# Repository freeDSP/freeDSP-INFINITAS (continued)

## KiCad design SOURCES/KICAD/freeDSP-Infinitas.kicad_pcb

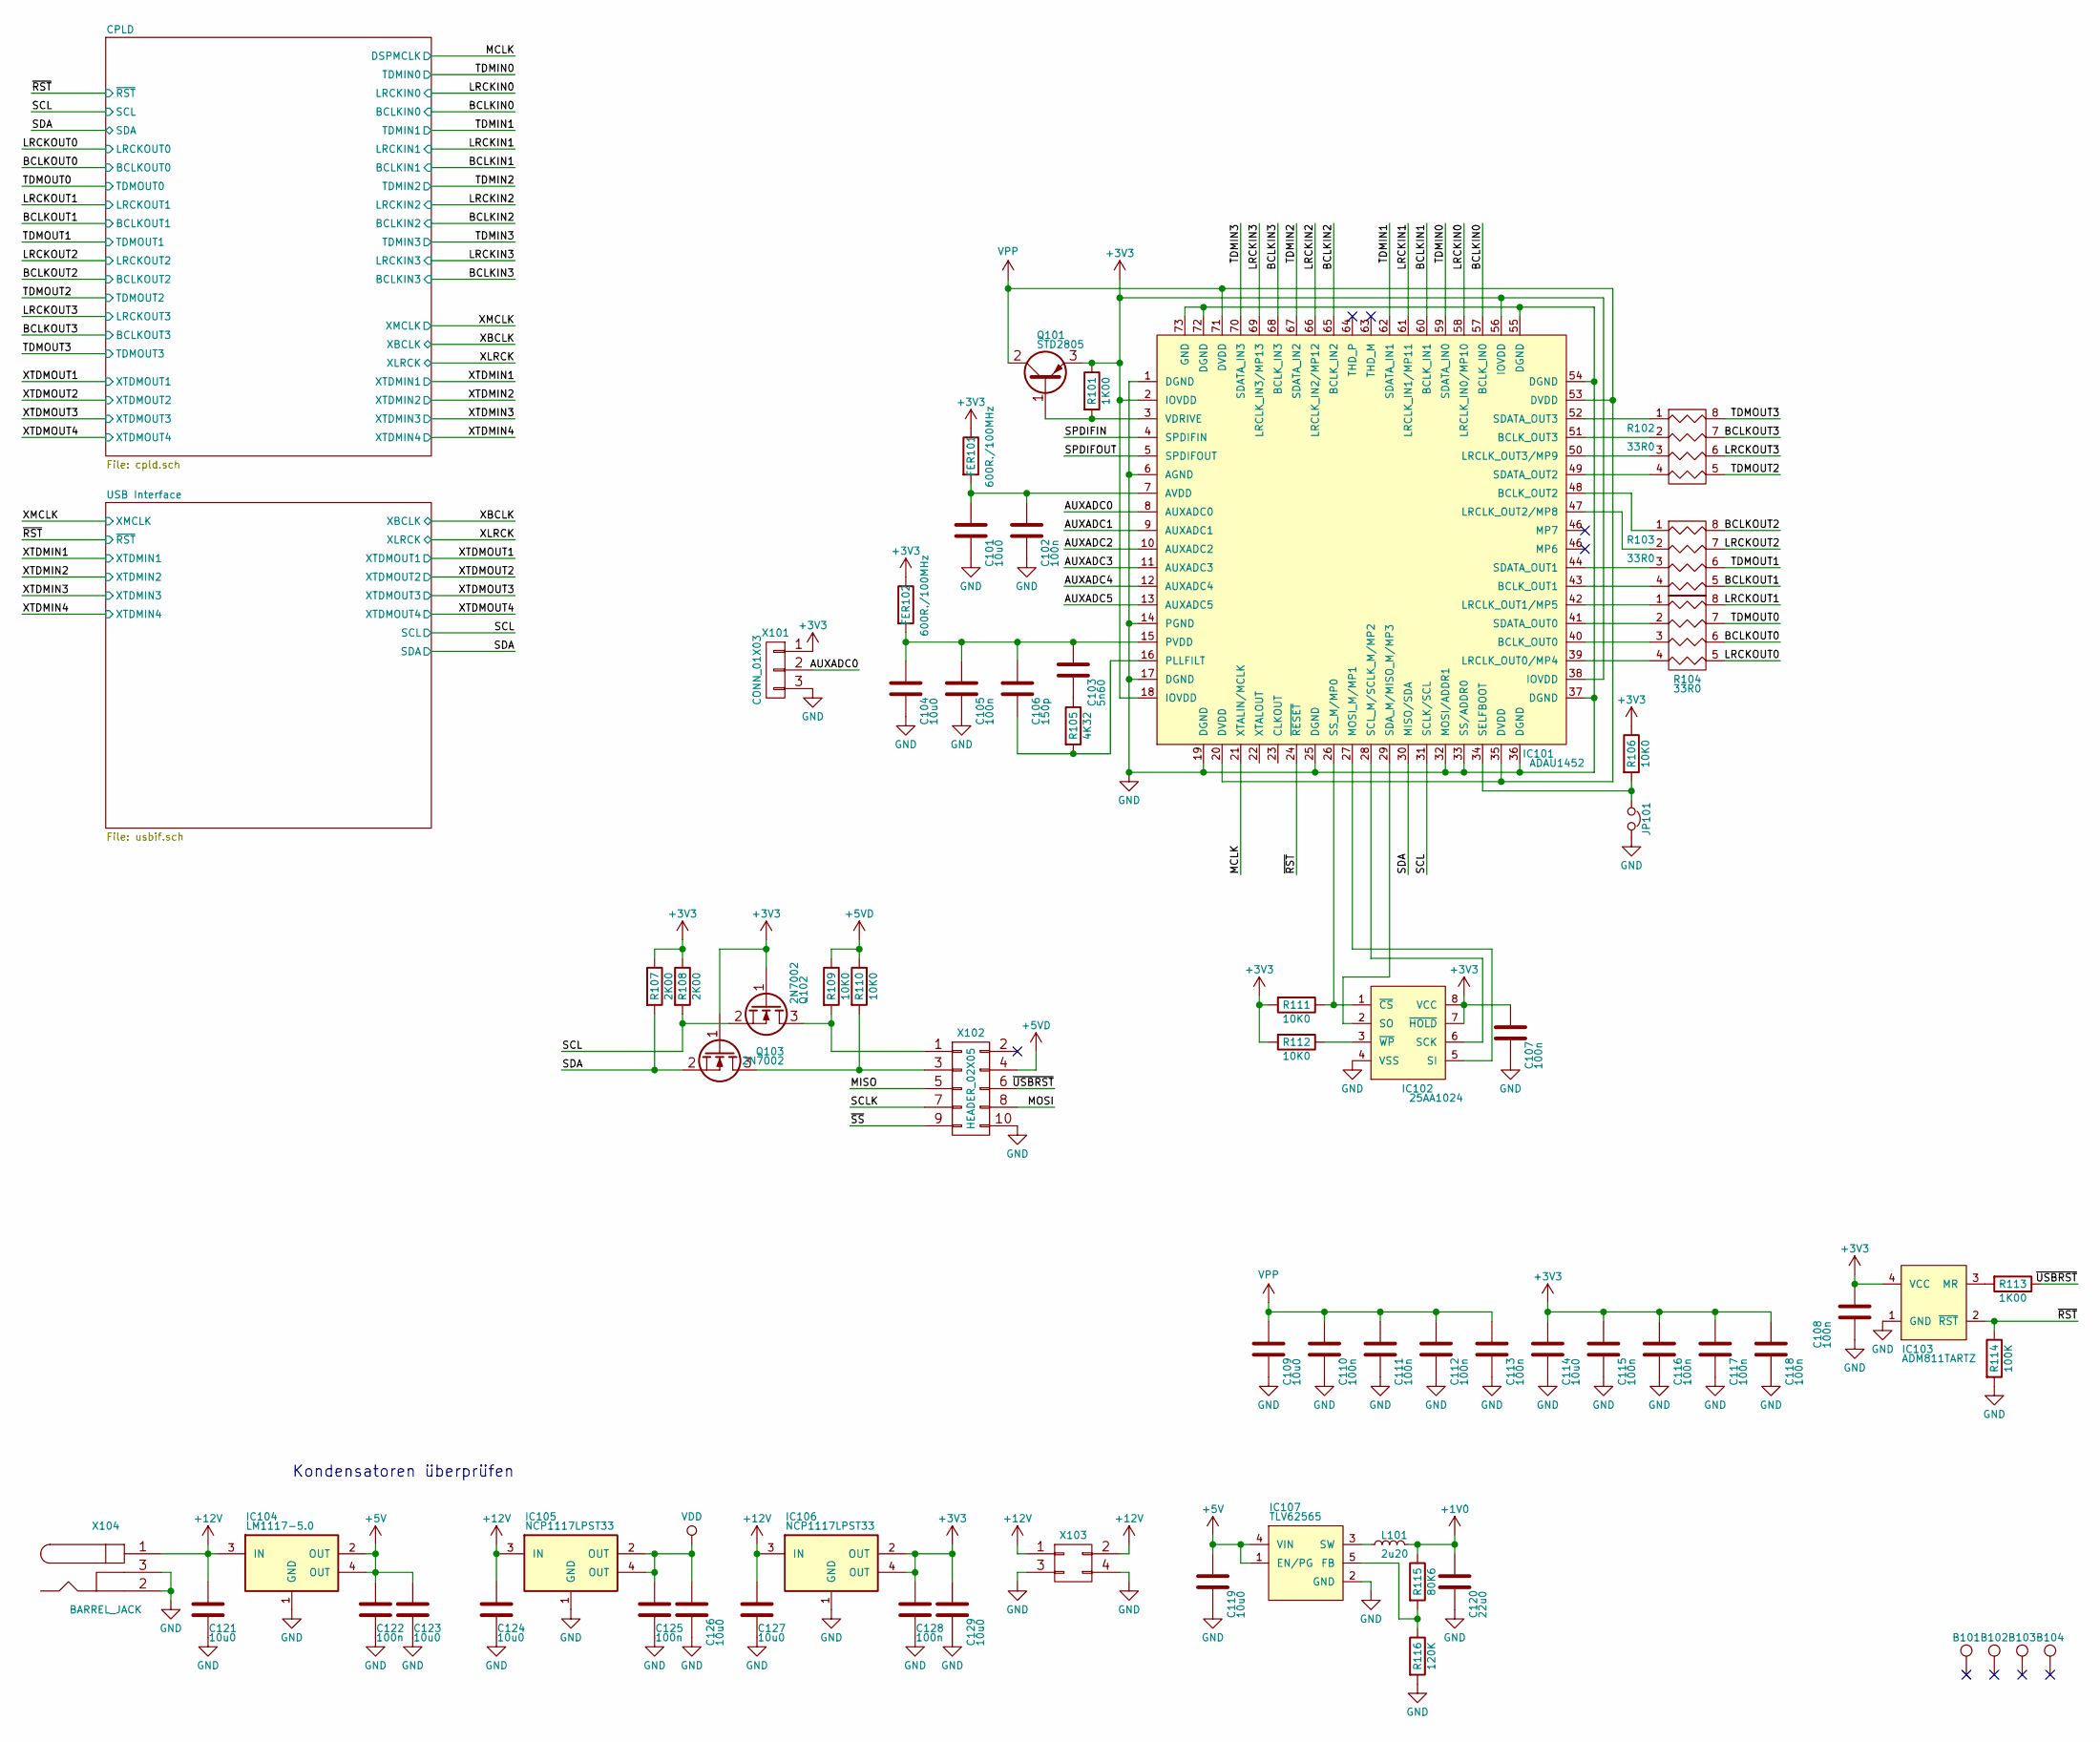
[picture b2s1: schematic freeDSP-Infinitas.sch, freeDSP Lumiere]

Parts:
B101, B102, B103, B104: TEST_1P; MountingHole_3.2mm_M3_DIN965_Pad
C101, C104, C109, C114, C119, C121, C123, C124, C126, C127, C129: 10u0; C0805-X7R
C102, C105, C107, C108, C110, C111, C112, C113, C115, C116, C117, C118, C122, C125, C128: 100n; C0805-X7R
C103: 5n60; C0805-X7R
C106: 150p; C0805-X7R
C120: 22u0; C0805-X7R
FER101, FER102: 600R./100MHz; C0805-RES
IC101: ADAU1452; QFP72_10x10_EP_Handsoldering
IC102: 25AA1024; SOIJ-8_5.3x5.3mm_Pitch1.27mm
IC103: ADM811TARTZ; SOT-143
IC104: LM1117-5.0; SOT-223
IC105, IC106: NCP1117LPST33; SOT-223
IC107: TLV62565; SOT-23-5
JP101: Jumper; Pin_Header_Straight_1x02
L101: 2u20; MCSDRH73B
Q101: STD2805; TO-252-2Lead
Q102, Q103: 2N7002; SOT-23
R101, R113: 1K00; C0805-RES
R102, R103, R104: 33R0; R_Array_Convex_4x0603
R105: 4K32; C0805-RES
R106, R109, R110, R111, R112: 10K0; C0805-RES
R107, R108: 2K00; C0805-RES
R114: 100K; C0805-RES
R115: 80K6; C0805-RES
R116: 120K; C0805-RES
X101: CONN_01X03; Connector_Molex_PicoBlade_53047-0310
X102: HEADER_02X05; Pin_Header_Straight_2x05
X103: CONN_02X02; Connector_Microfit3_Header_02x02_Straight_43045-0428
X104: BARREL_JACK

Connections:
+1V0: C120.1, L101.2, R115.1; also elsewhere on the board
+3V3: C107.1, C108.1, C114.1, C115.1, C116.1, C117.1, C118.1, C128.1, C129.1, FER101.1, FER102.1, IC101.2 (IOVDD), IC101.18 (IOVDD), IC101.38 (IOVDD), IC101.56 (IOVDD), IC102.7 (~HOLD), IC102.8 (VCC), IC103.4 (VCC), IC106.2 (OUT), IC106.4 (OUT), Q101.3 (E), Q102.1 (G), Q103.1 (G), R101.1, R106.1, R107.1, R108.1, R111.2, R112.2, X101.1; also elsewhere on the board
+5V: C119.1, C122.1, C123.1, IC104.2 (OUT), IC104.4 (OUT), IC107.1 (EN/PG), IC107.4 (VIN); also elsewhere on the board
+5VD: R109.1, R110.1, X102.4
+12V: C121.1, C124.1, C127.1, IC104.3 (IN), IC105.3 (IN), IC106.3 (IN), X103.1, X103.2, X104.1; also elsewhere on the board
/AUXADC0: IC101.8 (AUXADC0), X101.2
/BCLKIN0: IC101.57 (BCLK_IN0); also elsewhere on the board
/BCLKIN1: IC101.60 (BCLK_IN1); also elsewhere on the board
/BCLKIN2: IC101.65 (BCLK_IN2); also elsewhere on the board
/BCLKIN3: IC101.68 (BCLK_IN3); also elsewhere on the board
/BCLKOUT0: R104.6 (R3); also elsewhere on the board
/BCLKOUT1: R103.5 (R4); also elsewhere on the board
/BCLKOUT2: R103.8 (R1); also elsewhere on the board
/BCLKOUT3: R102.7 (R2); also elsewhere on the board
/LRCKIN0: IC101.58 (LRCLK_IN0/MP10); also elsewhere on the board
/LRCKIN1: IC101.61 (LRCLK_IN1/MP11); also elsewhere on the board
/LRCKIN2: IC101.66 (LRCLK_IN2/MP12); also elsewhere on the board
/LRCKIN3: IC101.69 (LRCLK_IN3/MP13); also elsewhere on the board
/LRCKOUT0: R104.5 (R4); also elsewhere on the board
/LRCKOUT1: R104.8 (R1); also elsewhere on the board
/LRCKOUT2: R103.7 (R2); also elsewhere on the board
/LRCKOUT3: R102.6 (R3); also elsewhere on the board
/MCLK: IC101.21 (XTALIN/MCLK); also elsewhere on the board
/SCL: IC101.31 (SCLK/SCL), Q102.2 (S), R108.2; also elsewhere on the board
/SDA: IC101.30 (MISO/SDA), Q103.2 (S), R107.2; also elsewhere on the board
/TDMIN0: IC101.59 (SDATA_IN0); also elsewhere on the board
/TDMIN1: IC101.62 (SDATA_IN1); also elsewhere on the board
/TDMIN2: IC101.67 (SDATA_IN2); also elsewhere on the board
/TDMIN3: IC101.70 (SDATA_IN3); also elsewhere on the board
/TDMOUT0: R104.7 (R2); also elsewhere on the board
/TDMOUT1: R103.6 (R3); also elsewhere on the board
/TDMOUT2: R102.5 (R4); also elsewhere on the board
/TDMOUT3: R102.8 (R1); also elsewhere on the board
/~RST: IC101.24 (~RESET), IC103.2 (~RST), R114.1; also elsewhere on the board
/~USBRST: R113.1, X102.6
unnamed: C101.1, C102.1, FER101.2, IC101.7 (AVDD)
unnamed: C103.1, C104.1, C105.1, C106.1, FER102.2, IC101.15 (PVDD)
unnamed: C103.2, R105.1
unnamed: C106.2, IC101.16 (PLLFILT), R105.2
unnamed: IC101.3 (VDRIVE), Q101.1 (B), R101.2
unnamed: IC101.26 (SS_M/MP0), IC102.1 (~CS), R111.1
unnamed: IC101.27 (MOSI_M/MP1), IC102.5 (SI)
unnamed: IC101.28 (SCL_M/SCLK_M/MP2), IC102.6 (SCK)
unnamed: IC101.29 (SDA_M/MISO_M/MP3), IC102.2 (SO)
unnamed: IC101.34 (SELFBOOT), JP101.1, R106.2
unnamed: IC101.39 (LRCLK_OUT0/MP4), R104.4
unnamed: IC101.40 (BCLK_OUT0), R104.3
unnamed: IC101.41 (SDATA_OUT0), R104.2
unnamed: IC101.42 (LRCLK_OUT1/MP5), R104.1
unnamed: IC101.43 (BCLK_OUT1), R103.4
unnamed: IC101.44 (SDATA_OUT1), R103.3
unnamed: IC101.47 (LRCLK_OUT2/MP8), R103.2
unnamed: IC101.48 (BCLK_OUT2), R103.1
unnamed: IC101.49 (SDATA_OUT2), R102.4
unnamed: IC101.50 (LRCLK_OUT3/MP9), R102.3
unnamed: IC101.51 (BCLK_OUT3), R102.2
unnamed: IC101.52 (SDATA_OUT3), R102.1
unnamed: IC102.3 (~WP), R112.1
unnamed: IC103.3 (MR), R113.2
unnamed: IC107.3 (SW), L101.1
unnamed: IC107.5 (FB), R115.2, R116.1
unnamed: Q102.3 (D), R109.2, X102.1
unnamed: Q103.3 (D), R110.2, X102.3
VDD: C125.1, C126.1, IC105.2 (OUT), IC105.4 (OUT); also elsewhere on the board
VPP: C109.1, C110.1, C111.1, C112.1, C113.1, IC101.20 (DVDD), IC101.35 (DVDD), IC101.53 (DVDD), IC101.71 (DVDD), Q101.2 (C)

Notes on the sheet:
Kondensatoren überprüfen

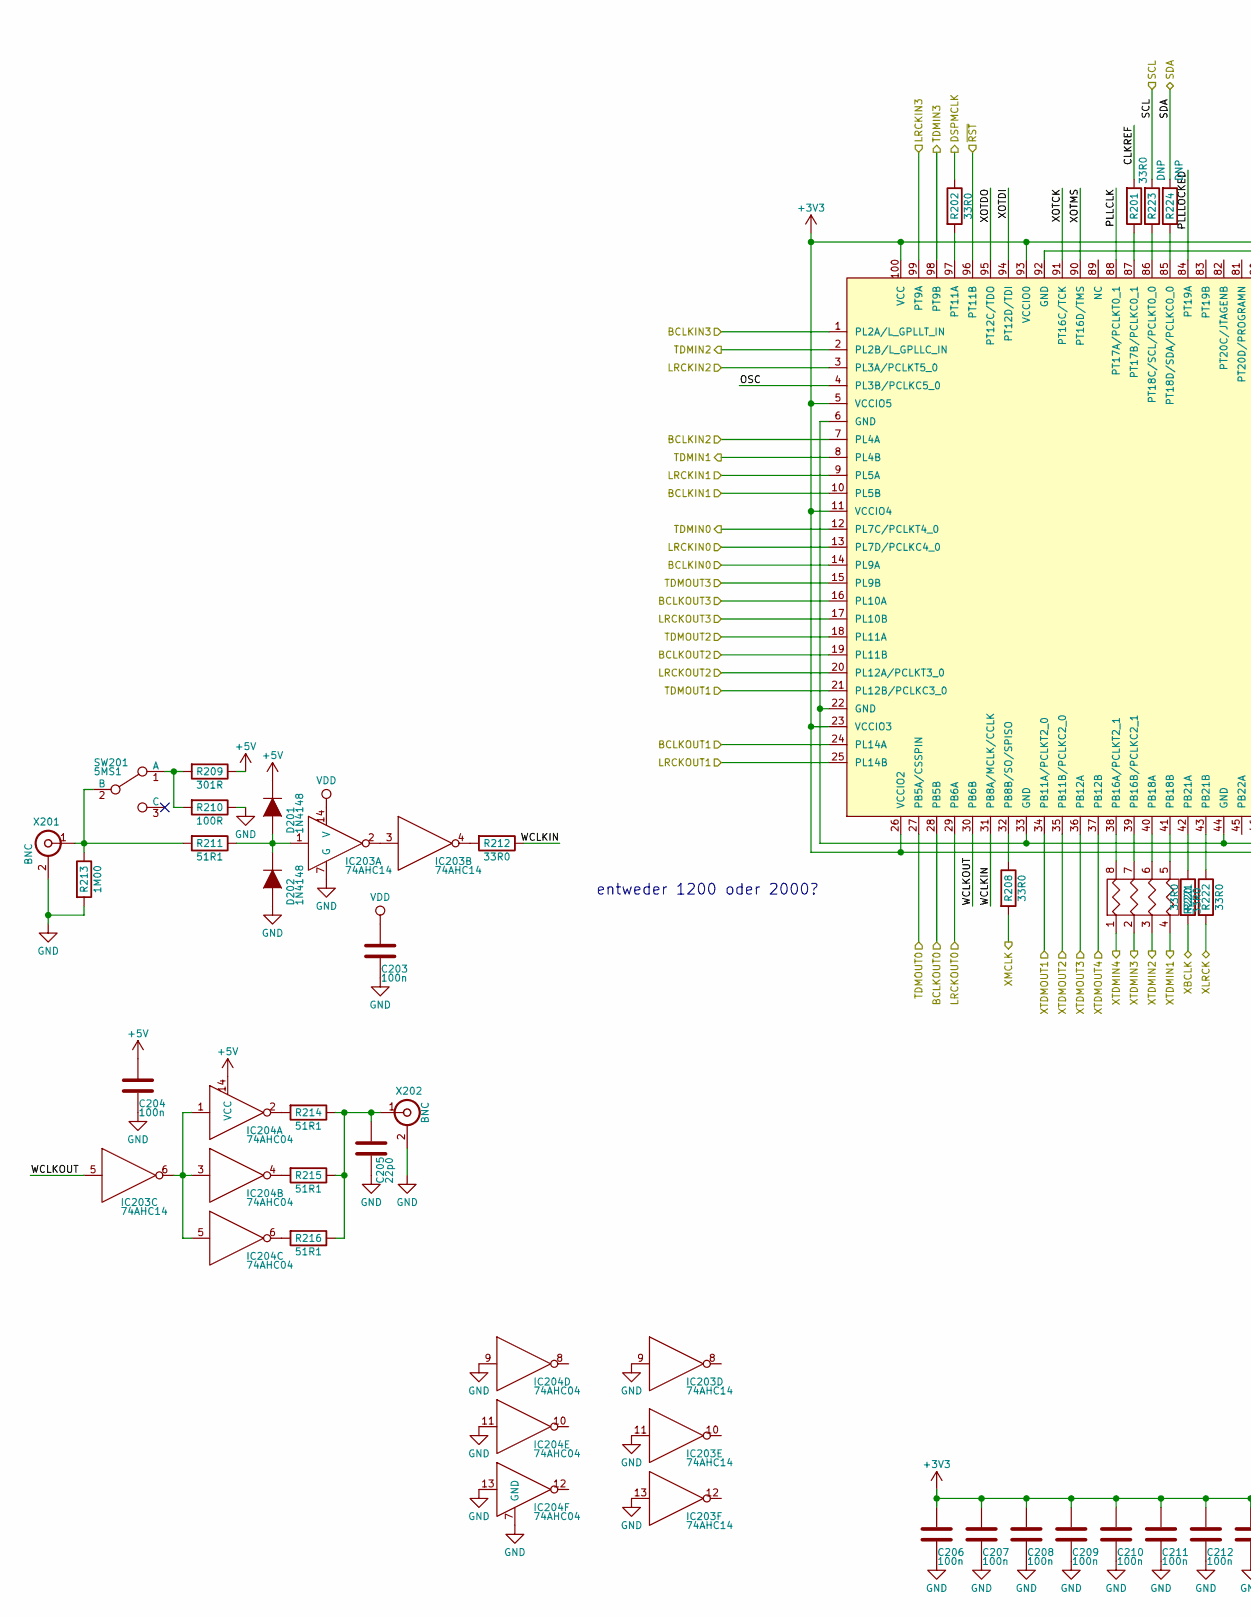
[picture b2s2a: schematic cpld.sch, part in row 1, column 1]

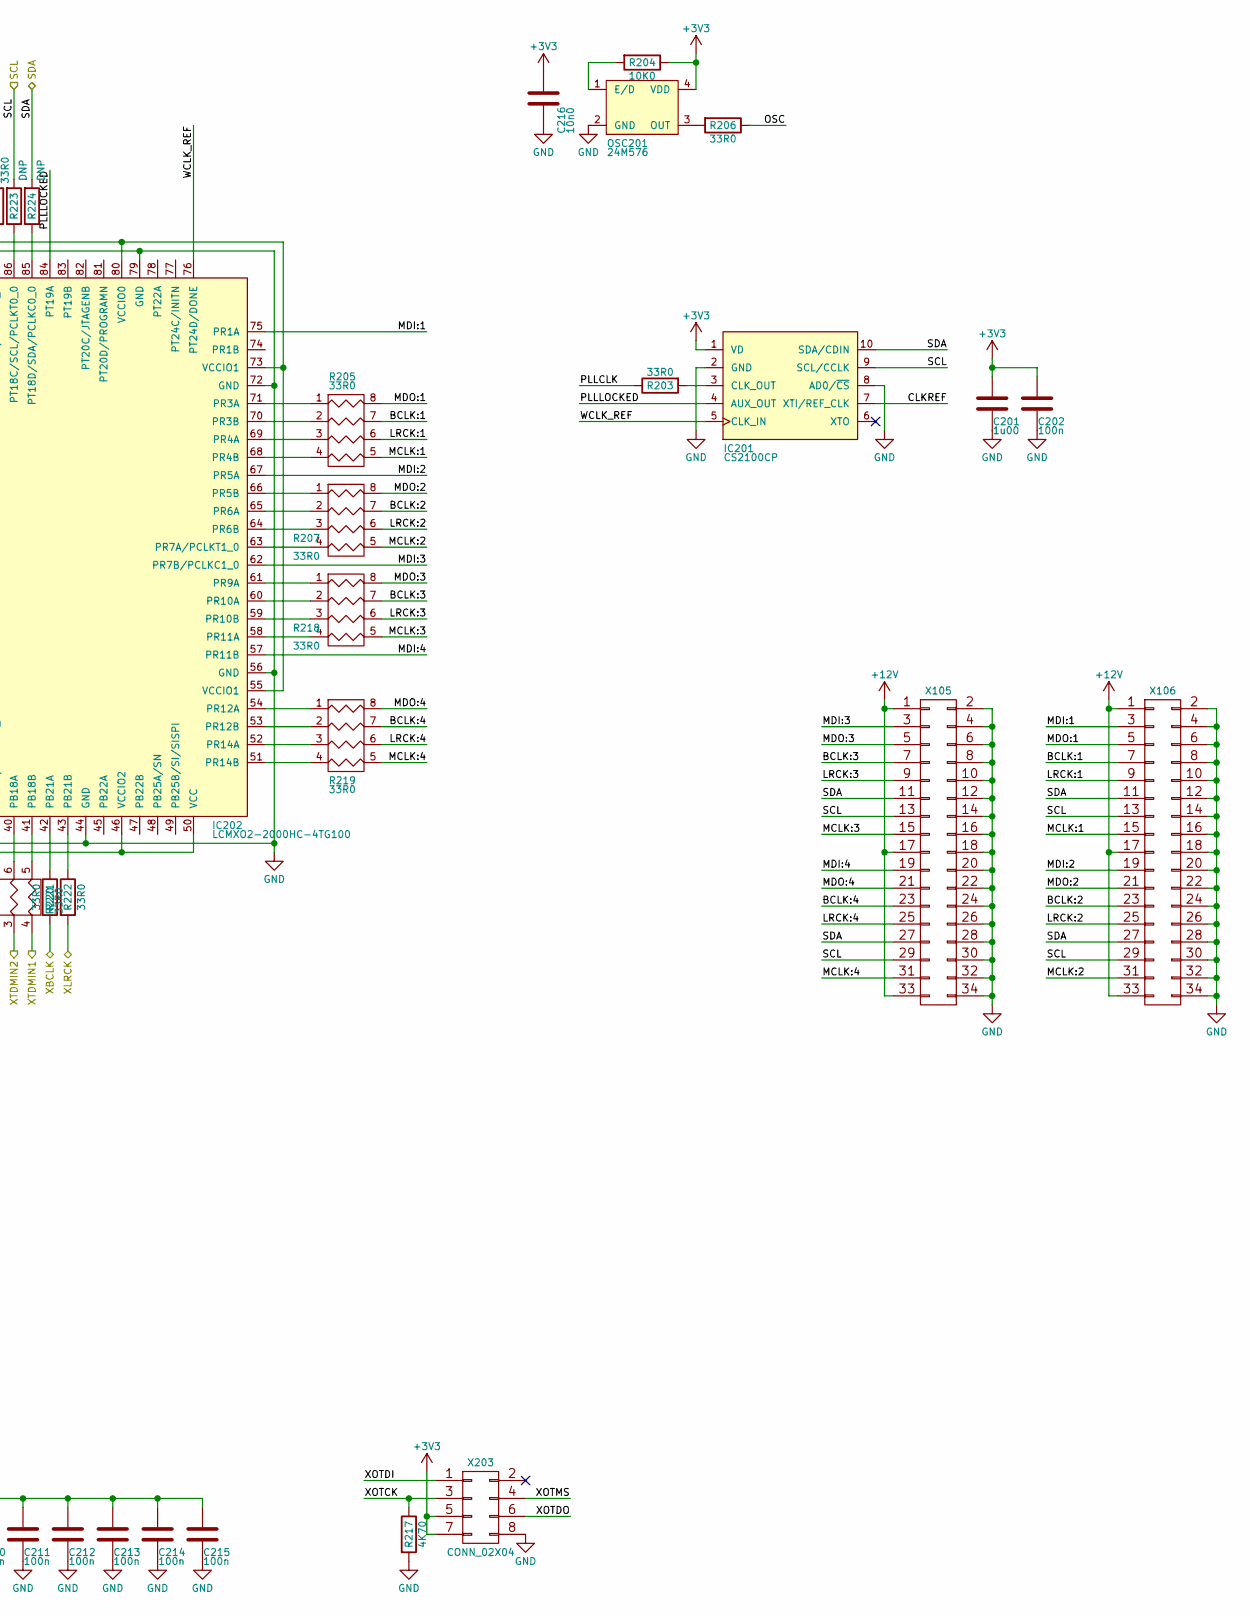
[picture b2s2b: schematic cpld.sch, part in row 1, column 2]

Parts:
C201: 1u00; C0805-X7R
C202, C203, C204, C206, C207, C208, C209, C210, C211, C212, C213, C214, C215: 100n; C0805-X7R
C205: 22p0; C0805-X7R
C216: 10n0; C0805-X7R
D201, D202: 1N4148; MiniMELF_Standard
IC201: CS2100CP; MSOP-10_3x3mm_Pitch0.5mm
IC202: LCMXO2-2000HC-4TG100; TQFP-100_14x14mm_Pitch0.5mm
IC203: 74AHC14; SOIC14_3.9x8.7mm_Pitch1.27mm
IC204: 74AHC04; SOIC14_3.9x8.7mm_Pitch1.27mm
OSC201: 24M576; ASFL1
R201, R202, R203, R206, R208, R212, R221, R222: 33R0; C0805-RES
R204: 10K0; C0805-RES
R205, R207, R218, R219, R220: 33R0; R_Array_Convex_4x0603
R209: 301R; C0805-RES
R210: 100R; C0805-RES
R211, R214, R215, R216: 51R1; C0805-RES
R213: 1M00; C0805-RES
R217: 4K70; C0805-RES
R223, R224: DNP; C0805-RES
SW201: 5MS1; 5MS1-SPDT
X105, X106: CONN_02X17; IDC_Header_Straight_34pins
X201, X202: BNC; BNC-H
X203: CONN_02X04; Pin_Header_Straight_2x04

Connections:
+3V3: C201.1, C202.1, C206.1, C207.1, C208.1, C209.1, C210.1, C211.1, C212.1, C213.1, C214.1, C215.1, C216.1, IC201.1 (VD), IC202.5 (VCCIO5), IC202.11 (VCCIO4), IC202.23 (VCCIO3), IC202.26 (VCCIO2), IC202.46 (VCCIO2), IC202.50 (VCC), IC202.55 (VCCIO1), IC202.73 (VCCIO1), IC202.80 (VCCIO0), IC202.93 (VCCIO0), IC202.100 (VCC), OSC201.4 (VDD), R204.1, X203.5, X203.7; also elsewhere on the board
+5V: C204.1, D201.1 (K), IC204.14 (VCC), R209.1; also elsewhere on the board
+12V: X105.1, X105.17, X105.33, X106.1, X106.17, X106.33; also elsewhere on the board
/BCLKIN0: IC202.14 (PL9A); also elsewhere on the board
/BCLKIN1: IC202.10 (PL5B); also elsewhere on the board
/BCLKIN2: IC202.7 (PL4A); also elsewhere on the board
/BCLKIN3: IC202.1 (PL2A/L_GPLLT_IN); also elsewhere on the board
/BCLKOUT0: IC202.28 (PB5B); also elsewhere on the board
/BCLKOUT1: IC202.24 (PL14A); also elsewhere on the board
/BCLKOUT2: IC202.19 (PL11B); also elsewhere on the board
/BCLKOUT3: IC202.16 (PL10A); also elsewhere on the board
/CPLD/BCLK:1: R205.7 (R2), X106.7
/CPLD/BCLK:2: R207.7 (R2), X106.23
/CPLD/BCLK:3: R218.7 (R2), X105.7
/CPLD/BCLK:4: R219.7 (R2), X105.23
/CPLD/CLKREF: IC201.7 (XTI/REF_CLK), R201.2
/CPLD/LRCK:1: R205.6 (R3), X106.9
/CPLD/LRCK:2: R207.6 (R3), X106.25
/CPLD/LRCK:3: R218.6 (R3), X105.9
/CPLD/LRCK:4: R219.6 (R3), X105.25
/CPLD/MCLK:1: R205.5 (R4), X106.15
/CPLD/MCLK:2: R207.5 (R4), X106.31
/CPLD/MCLK:3: R218.5 (R4), X105.15
/CPLD/MCLK:4: R219.5 (R4), X105.31
/CPLD/MDI:1: IC202.75 (PR1A), X106.3
/CPLD/MDI:2: IC202.67 (PR5A), X106.19
/CPLD/MDI:3: IC202.62 (PR7B/PCLKC1_0), X105.3
/CPLD/MDI:4: IC202.57 (PR11B), X105.19
/CPLD/MDO:1: R205.8 (R1), X106.5
/CPLD/MDO:2: R207.8 (R1), X106.21
/CPLD/MDO:3: R218.8 (R1), X105.5
/CPLD/MDO:4: R219.8 (R1), X105.21
/CPLD/OSC: IC202.4 (PL3B/PCLKC5_0), R206.1
/CPLD/PLLCLK: IC202.88 (PT17A/PCLKT0_1), R203.1
/CPLD/PLLLOCKED: IC201.4 (AUX_OUT), IC202.84 (PT19A)
/CPLD/WCLKIN: IC202.31 (PB8A/MCLK/CCLK), R212.1
/CPLD/WCLKOUT: IC202.30 (PB6B), IC203.5
/CPLD/WCLK_REF: IC201.5 (CLK_IN), IC202.76 (PT24D/DONE)
/CPLD/XOTCK: IC202.91 (PT16C/TCK), R217.1, X203.3
/CPLD/XOTDI: IC202.94 (PT12D/TDI), X203.1
/CPLD/XOTDO: IC202.95 (PT12C/TDO), X203.6
/CPLD/XOTMS: IC202.90 (PT16D/TMS), X203.4
/LRCKIN0: IC202.13 (PL7D/PCLKC4_0); also elsewhere on the board
/LRCKIN1: IC202.9 (PL5A); also elsewhere on the board
/LRCKIN2: IC202.3 (PL3A/PCLKT5_0); also elsewhere on the board
/LRCKIN3: IC202.99 (PT9A); also elsewhere on the board
/LRCKOUT0: IC202.29 (PB6A); also elsewhere on the board
/LRCKOUT1: IC202.25 (PL14B); also elsewhere on the board
/LRCKOUT2: IC202.20 (PL12A/PCLKT3_0); also elsewhere on the board
/LRCKOUT3: IC202.17 (PL10B); also elsewhere on the board
/MCLK: R202.1; also elsewhere on the board
/SCL: IC201.9 (SCL/CCLK), R223.2, X105.13, X105.29, X106.13, X106.29; also elsewhere on the board
/SDA: IC201.10 (SDA/CDIN), R224.2, X105.11, X105.27, X106.11, X106.27; also elsewhere on the board
/TDMIN0: IC202.12 (PL7C/PCLKT4_0); also elsewhere on the board
/TDMIN1: IC202.8 (PL4B); also elsewhere on the board
/TDMIN2: IC202.2 (PL2B/L_GPLLC_IN); also elsewhere on the board
/TDMIN3: IC202.98 (PT9B); also elsewhere on the board
/TDMOUT0: IC202.27 (PB5A/CSSPIN); also elsewhere on the board
/TDMOUT1: IC202.21 (PL12B/PCLKC3_0); also elsewhere on the board
/TDMOUT2: IC202.18 (PL11A); also elsewhere on the board
/TDMOUT3: IC202.15 (PL9B); also elsewhere on the board
/XBCLK: R221.2; also elsewhere on the board
/XLRCK: R222.2; also elsewhere on the board
/XMCLK: R208.2; also elsewhere on the board
/XTDMIN1: R220.4; also elsewhere on the board
/XTDMIN2: R220.3; also elsewhere on the board
/XTDMIN3: R220.2; also elsewhere on the board
/XTDMIN4: R220.1; also elsewhere on the board
/XTDMOUT1: IC202.34 (PB11A/PCLKT2_0); also elsewhere on the board
/XTDMOUT2: IC202.35 (PB11B/PCLKC2_0); also elsewhere on the board
/XTDMOUT3: IC202.36 (PB12A); also elsewhere on the board
/XTDMOUT4: IC202.37 (PB12B); also elsewhere on the board
/~RST: IC202.96 (PT11B); also elsewhere on the board
unnamed: C205.1, R214.1, R215.1, R216.1, X202.1 (In)
unnamed: D201.2 (A), D202.1 (K), IC203.1, R211.1
unnamed: IC201.3 (CLK_OUT), R203.2
unnamed: IC202.32 (PB8B/SO/SPISO), R208.1
unnamed: IC202.38 (PB16A/PCLKT2_1), R220.8 (R1)
unnamed: IC202.39 (PB16B/PCLKC2_1), R220.7 (R2)
unnamed: IC202.40 (PB18A), R220.6 (R3)
unnamed: IC202.41 (PB18B), R220.5 (R4)
unnamed: IC202.42 (PB21A), R221.1
unnamed: IC202.43 (PB21B), R222.1
unnamed: IC202.51 (PR14B), R219.4
unnamed: IC202.52 (PR14A), R219.3
unnamed: IC202.53 (PR12B), R219.2
unnamed: IC202.54 (PR12A), R219.1
unnamed: IC202.58 (PR11A), R218.4
unnamed: IC202.59 (PR10B), R218.3
unnamed: IC202.60 (PR10A), R218.2
unnamed: IC202.61 (PR9A), R218.1
unnamed: IC202.63 (PR7A/PCLKT1_0), R207.4
unnamed: IC202.64 (PR6B), R207.3
unnamed: IC202.65 (PR6A), R207.2
unnamed: IC202.66 (PR5B), R207.1
unnamed: IC202.68 (PR4B), R205.4
unnamed: IC202.69 (PR4A), R205.3
unnamed: IC202.70 (PR3B), R205.2
unnamed: IC202.71 (PR3A), R205.1
unnamed: IC202.85 (PT18D/SDA/PCLKC0_0), R224.1
unnamed: IC202.86 (PT18C/SCL/PCLKT0_0), R223.1
unnamed: IC202.87 (PT17B/PCLKC0_1), R201.1
unnamed: IC202.97 (PT11A), R202.2
unnamed: IC203.2, IC203.3
unnamed: IC203.4, R212.2
unnamed: IC203.6, IC204.1, IC204.3, IC204.5
unnamed: IC204.2, R214.2
unnamed: IC204.4, R215.2
unnamed: IC204.6, R216.2
unnamed: OSC201.1 (E/D), R204.2
unnamed: OSC201.3 (OUT), R206.2
unnamed: R209.2, R210.2, SW201.1 (A)
unnamed: R211.2, R213.1, SW201.2 (B), X201.1 (In)
VDD: C203.1, IC203.14 (V); also elsewhere on the board

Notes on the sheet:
entweder 1200 oder 2000?

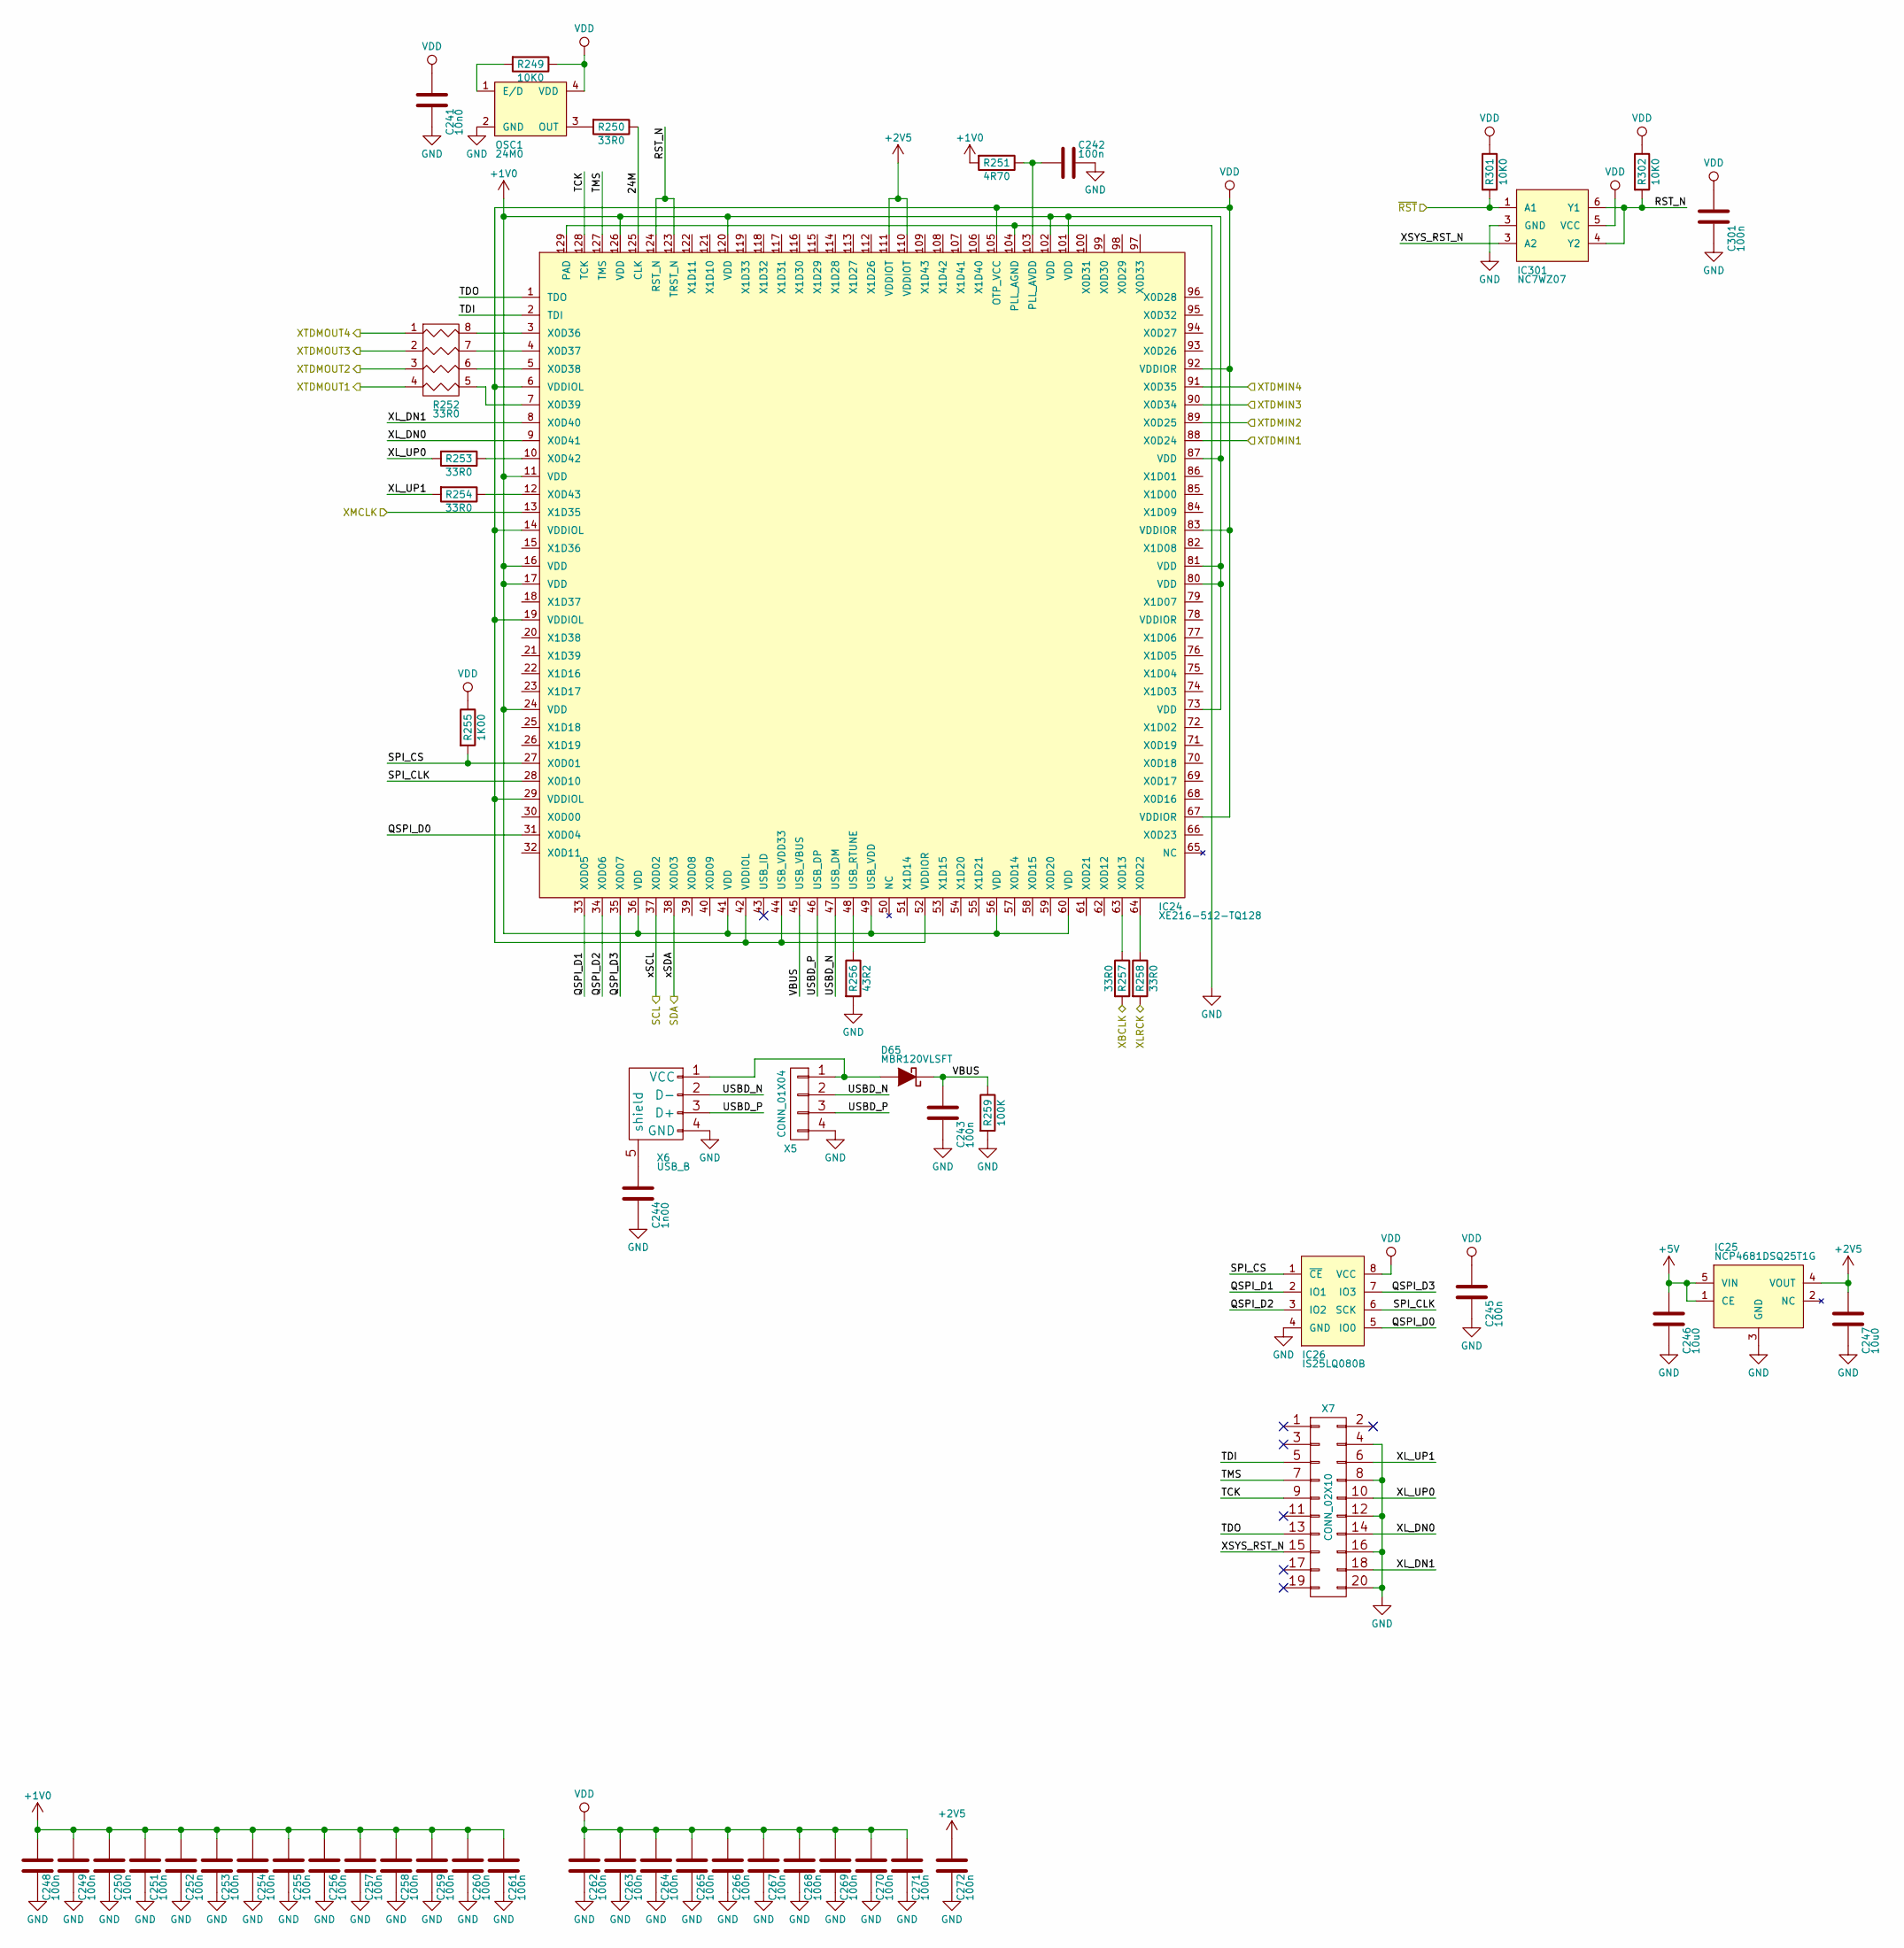
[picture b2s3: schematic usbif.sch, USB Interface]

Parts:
C241: 10n0; C0805-X7R
C242, C243, C245, C301: 100n; C0805-X7R
C244: 1n00; C0805-X7R
C246, C247: 10u0; C0805-X7R
C248, C249, C250, C251, C252, C253, C254, C255, C256, C257, C258, C259, C260, C261, C262, C263, C264, C265, C266, C267, C268, C269, C270, C271, C272: 100n; C_0402
D65: MBR120VLSFT; SOD-123
IC24: XE216-512-TQ128; TQFP-128_14x14mm_Pitch0.4mm_EP_Handsoldering
IC25: NCP4681DSQ25T1G; SC-70-5
IC26: IS25LQ080B; SOIC-8_3.9x4.9mm_Pitch1.27mm
IC301: NC7WZ07; SC-70-6
OSC1: 24M0; ASFL1
R249, R301, R302: 10K0; C0805-RES
R250, R253, R254, R257, R258: 33R0; C0805-RES
R251: 4R70; C0805-RES
R252: 33R0; R_Array_Convex_4x0603
R255: 1K00; C0805-RES
R256: 43R2; C0805-RES
R259: 100K; C0805-RES
X5: CONN_01X04; Pin_Header_Straight_1x04
X6: USB_B
X7: CONN_02X10; Pin_Header_Straight_2x10

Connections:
+1V0: C248.1, C249.1, C250.1, C251.1, C252.1, C253.1, C254.1, C255.1, C256.1, C257.1, C258.1, C259.1, C260.1, C261.1, IC24.11 (VDD), IC24.16 (VDD), IC24.17 (VDD), IC24.24 (VDD), IC24.36 (VDD), IC24.41 (VDD), IC24.49 (USB_VDD), IC24.56 (VDD), IC24.60 (VDD), IC24.73 (VDD), IC24.80 (VDD), IC24.81 (VDD), IC24.87 (VDD), IC24.101 (VDD), IC24.102 (VDD), IC24.120 (VDD), IC24.126 (VDD), R251.2; also elsewhere on the board
+2V5: C247.1, C272.1, IC24.110 (VDDIOT), IC24.111 (VDDIOT), IC25.4 (VOUT)
+5V: C246.1, IC25.1 (CE), IC25.5 (VIN); also elsewhere on the board
/SCL: IC24.37 (X0D02); also elsewhere on the board
/SDA: IC24.38 (X0D03); also elsewhere on the board
/USB Interface/24M: IC24.125 (CLK), R250.1
/USB Interface/QSPI_D0: IC24.31 (X0D04), IC26.5 (IO0)
/USB Interface/QSPI_D1: IC24.33 (X0D05), IC26.2 (IO1)
/USB Interface/QSPI_D2: IC24.34 (X0D06), IC26.3 (IO2)
/USB Interface/QSPI_D3: IC24.35 (X0D07), IC26.7 (IO3)
/USB Interface/RST_N: IC24.123 (TRST_N), IC24.124 (RST_N), IC301.4 (Y2), IC301.6 (Y1), R302.2
/USB Interface/SPI_CLK: IC24.28 (X0D10), IC26.6 (SCK)
/USB Interface/SPI_CS: IC24.27 (X0D01), IC26.1 (~CE), R255.2
/USB Interface/TCK: IC24.128 (TCK), X7.9
/USB Interface/TDI: IC24.2 (TDI), X7.5
/USB Interface/TDO: IC24.1 (TDO), X7.13
/USB Interface/TMS: IC24.127 (TMS), X7.7
/USB Interface/USBD_N: IC24.47 (USB_DM), X5.2, X6.2 (D-)
/USB Interface/USBD_P: IC24.46 (USB_DP), X5.3, X6.3 (D+)
/USB Interface/VBUS: C243.1, D65.1 (K), IC24.45 (USB_VBUS), R259.1
/USB Interface/XL_DN0: IC24.9 (X0D41), X7.14
/USB Interface/XL_DN1: IC24.8 (X0D40), X7.18
/USB Interface/XL_UP0: R253.2, X7.10
/USB Interface/XL_UP1: R254.2, X7.6
/XBCLK: R257.2; also elsewhere on the board
/XLRCK: R258.2; also elsewhere on the board
/XMCLK: IC24.13 (X1D35); also elsewhere on the board
/XTDMIN1: IC24.88 (X0D24); also elsewhere on the board
/XTDMIN2: IC24.89 (X0D25); also elsewhere on the board
/XTDMIN3: IC24.90 (X0D34); also elsewhere on the board
/XTDMIN4: IC24.91 (X0D35); also elsewhere on the board
/XTDMOUT1: R252.4; also elsewhere on the board
/XTDMOUT2: R252.3; also elsewhere on the board
/XTDMOUT3: R252.2; also elsewhere on the board
/XTDMOUT4: R252.1; also elsewhere on the board
/~RST: IC301.1 (A1), R301.2; also elsewhere on the board
unnamed: C242.2, IC24.103 (PLL_AVDD), R251.1
unnamed: C244.1, X6.5 (shield)
unnamed: D65.2 (A), X5.1, X6.1 (VCC)
unnamed: IC24.3 (X0D36), R252.8 (R1)
unnamed: IC24.4 (X0D37), R252.7 (R2)
unnamed: IC24.5 (X0D38), R252.6 (R3)
unnamed: IC24.7 (X0D39), R252.5 (R4)
unnamed: IC24.10 (X0D42), R253.1
unnamed: IC24.12 (X0D43), R254.1
unnamed: IC24.48 (USB_RTUNE), R256.1
unnamed: IC24.63 (X0D13), R257.1
unnamed: IC24.64 (X0D22), R258.1
unnamed: OSC1.1 (E/D), R249.2
unnamed: OSC1.3 (OUT), R250.2
VDD: C241.1, C245.1, C262.1, C263.1, C264.1, C265.1, C266.1, C267.1, C268.1, C269.1, C270.1, C271.1, C301.1, IC24.6 (VDDIOL), IC24.14 (VDDIOL), IC24.19 (VDDIOL), IC24.29 (VDDIOL), IC24.42 (VDDIOL), IC24.44 (USB_VDD33), IC24.52 (VDDIOR), IC24.67 (VDDIOR), IC24.83 (VDDIOR), IC24.92 (VDDIOR), IC24.105 (OTP_VCC), IC26.8 (VCC), IC301.5 (VCC), OSC1.4 (VDD), R249.1, R255.1, R301.1, R302.1; also elsewhere on the board

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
